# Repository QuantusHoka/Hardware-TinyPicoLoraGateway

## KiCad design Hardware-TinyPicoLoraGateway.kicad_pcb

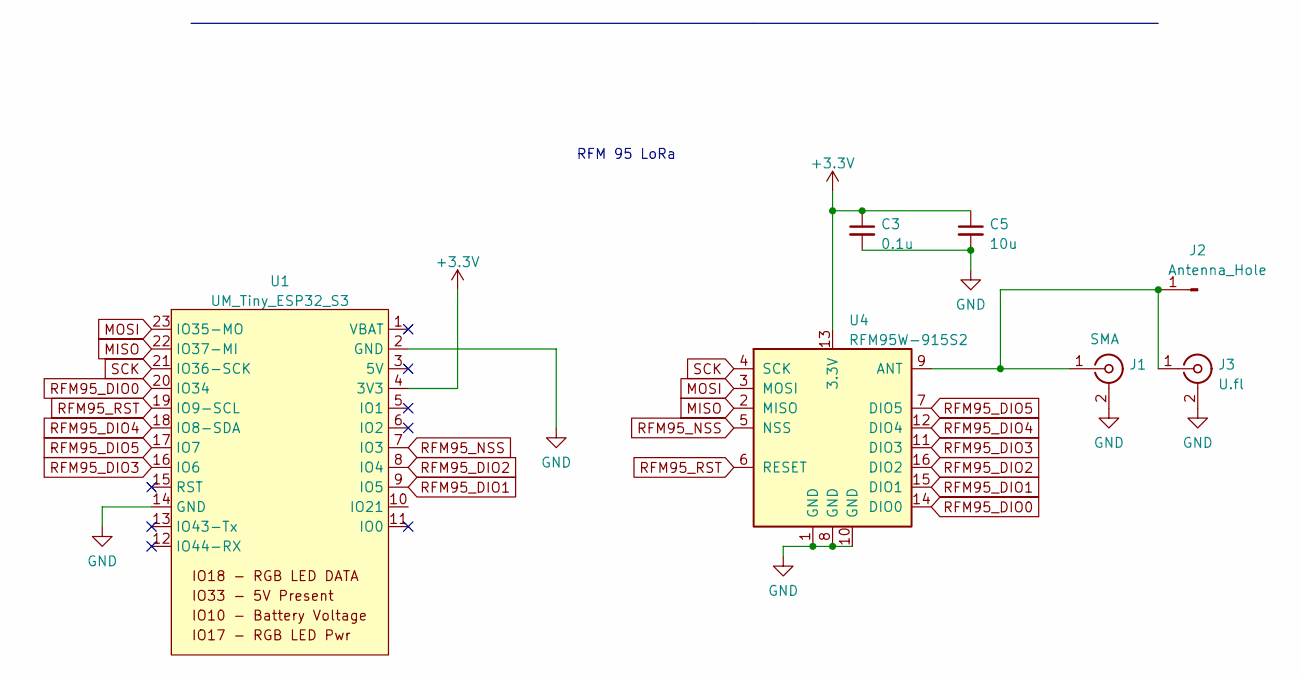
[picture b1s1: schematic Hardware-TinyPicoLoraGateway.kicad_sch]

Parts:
C3: 0.1u; C_1206_3216Metric; LCSC Part C110253
C5: 10u; CP_EIA-3216-18_Kemet-A; LCSC Part C7177
J1: SMA; SMA_Amphenol_132289_EdgeMount; LCSC Part C496550
J2: Antenna_Hole; PinHeader_1x01_P2.54mm_Vertical
J3: U.fl; U.FL_Hirose_U.FL-R-SMT-1_Vertical; LCSC Part C88374
U1: UM_Tiny_ESP32_S3; TinyS3
U4: RFM95W-915S2; HOPERF_RFM9XW_SMD

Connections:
+3.3V: C3.1, C5.1, U1.4 (3V3), U4.13 (3.3V)
GND: C3.2, C5.2, J1.2 (Ext), J3.2 (Ext), U1.2 (GND), U1.14 (GND), U4.1 (GND), U4.8 (GND), U4.10 (GND)
MISO: U1.22 (IO37-MI), U4.2 (MISO)
MOSI: U1.23 (IO35-MO), U4.3 (MOSI)
unnamed: J1.1 (In), J2.1, J3.1 (In), U4.9 (ANT)
RFM95_DIO0: U1.20 (IO34), U4.14 (DIO0)
RFM95_DIO1: U1.9 (IO5), U4.15 (DIO1)
RFM95_DIO2: U1.8 (IO4), U4.16 (DIO2)
RFM95_DIO3: U1.16 (IO6), U4.11 (DIO3)
RFM95_DIO4: U1.18 (IO8-SDA), U4.12 (DIO4)
RFM95_DIO5: U1.17 (IO7), U4.7 (DIO5)
RFM95_NSS: U1.7 (IO3), U4.5 (NSS)
RFM95_RST: U1.19 (IO9-SCL), U4.6 (RESET)
SCK: U1.21 (IO36-SCK), U4.4 (SCK)

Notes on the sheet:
RFM 95 LoRa

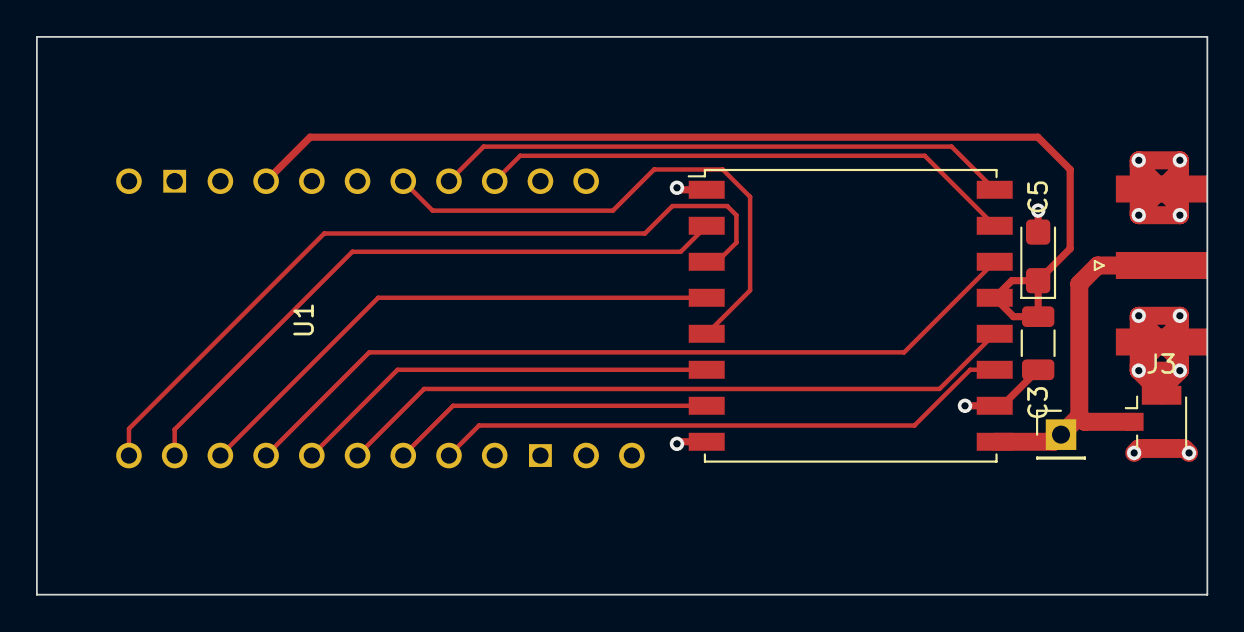
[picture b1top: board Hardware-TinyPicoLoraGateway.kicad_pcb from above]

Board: 2 copper layers, 65.0 x 31.0 mm, 7 parts (0 on the bottom side), 14 nets.

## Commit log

2023-01-26 Update 2023-01-25
